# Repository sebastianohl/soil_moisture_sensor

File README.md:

# Homie soil moisture sensor 

Needed Hardware:
* EPS12F
* soil moisture sensor
* solar panel
* LiPo battery 18450
* solar power regulator

Configuration:
* use idy.py menuconfig to parameters (e.g. WiFi Password, MQTT Settings...)

Software:
* ESP-IDF Package
* Eclipse (or any other IDE)

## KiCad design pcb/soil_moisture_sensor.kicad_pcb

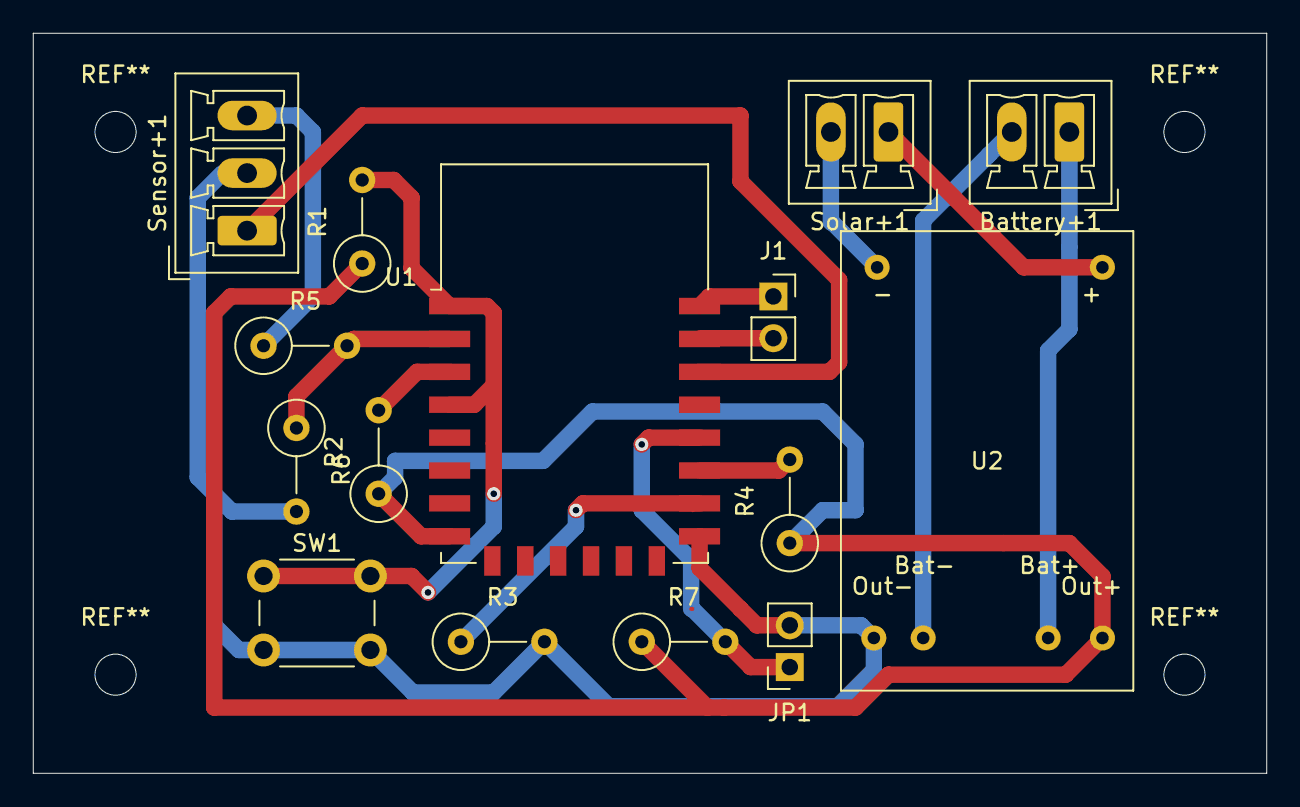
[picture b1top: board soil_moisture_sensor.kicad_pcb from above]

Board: 2 copper layers, 75.0 x 45.0 mm, 15 parts (0 on the bottom side), 16 nets.

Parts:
Battery+1: Battery; PhoenixContact_MCV_1,5_2-G-3.5_1x02_P3.50mm_Vertical
J1: Serial; PinSocket_1x02_P2.54mm_Vertical
JP1: Flash; PinSocket_1x02_P2.54mm_Vertical
R1, R2, R3, R4, R7: 10k; R_Axial_DIN0309_L9.0mm_D3.2mm_P5.08mm_Vertical
R5: 220k; R_Axial_DIN0309_L9.0mm_D3.2mm_P5.08mm_Vertical
R6: 100k; R_Axial_DIN0309_L9.0mm_D3.2mm_P5.08mm_Vertical
SW1: Reset; SW_PUSH_6mm_H4.3mm
Sensor+1: Sensor; PhoenixContact_MCV_1,5_3-G-3.5_1x03_P3.50mm_Vertical
Solar+1: Solar; PhoenixContact_MCV_1,5_2-G-3.5_1x02_P3.50mm_Vertical
U1: ESP-12F; ESP-12E
U2: SolarRegulator

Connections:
unnamed: Battery+1.1, U2.5
unnamed: Battery+1.2, U2.4
unnamed: J1.1, U1.22
unnamed: J1.2, U1.21
unnamed: JP1.1, R7.2, U1.18
unnamed: JP1.2, R3.2, R6.2, SW1.2, Sensor+1.2, U1.15, U2.3
unnamed: R1.1, R2.1, R4.1, R7.1, U1.8, U2.6
unnamed: R1.2, SW1.1, U1.1, U1.4
unnamed: R2.2, U1.3
unnamed: R3.1, U1.16
unnamed: R4.2, U1.17
unnamed: R5.1, Sensor+1.3
unnamed: R5.2, R6.1, U1.2
unnamed: Sensor+1.1, U1.20
unnamed: Solar+1.1, U2.2
unnamed: Solar+1.2, U2.1

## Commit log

2020-08-26 flashable version, no function yet
2020-08-27 adding adc read
2020-10-28 move to vscode
2020-11-04 adding pcb
2021-01-02 fix subscribe on reconnect
2021-01-06 move devenv to docker in vscode
2021-01-06 remove temp file, move env variables to container startup
2021-03-04 normalize volate value to percent
2021-03-12 change scaling
2021-03-14 adding ota
2021-03-14 prevent inifite ota loop, set version and ota partition in homie data
2021-03-16 set hostname, accept ota urls via mqtt
2021-03-26 adding remote log
2021-03-27 adding mac to hostname for syslog
